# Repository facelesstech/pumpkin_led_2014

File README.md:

pumpkin_led_2014
================

Candle replacement for a Halloween pumpkin 2014 edition

Blog post explaining it all can be found here

https://facelesstech.wordpress.com/2014/10/30/pumpkin-candle-replacement-2014-edition-pumpkin_led/

Video of pumpkin led in action

http://youtu.be/Q0YgAvuTLzo?list=UUuK2SlZlnsWDYSvBv1lbuAwhttp://youtu.be/Q0YgAvuTLzo?list=UUuK2SlZlnsWDYSvBv1lbuAw

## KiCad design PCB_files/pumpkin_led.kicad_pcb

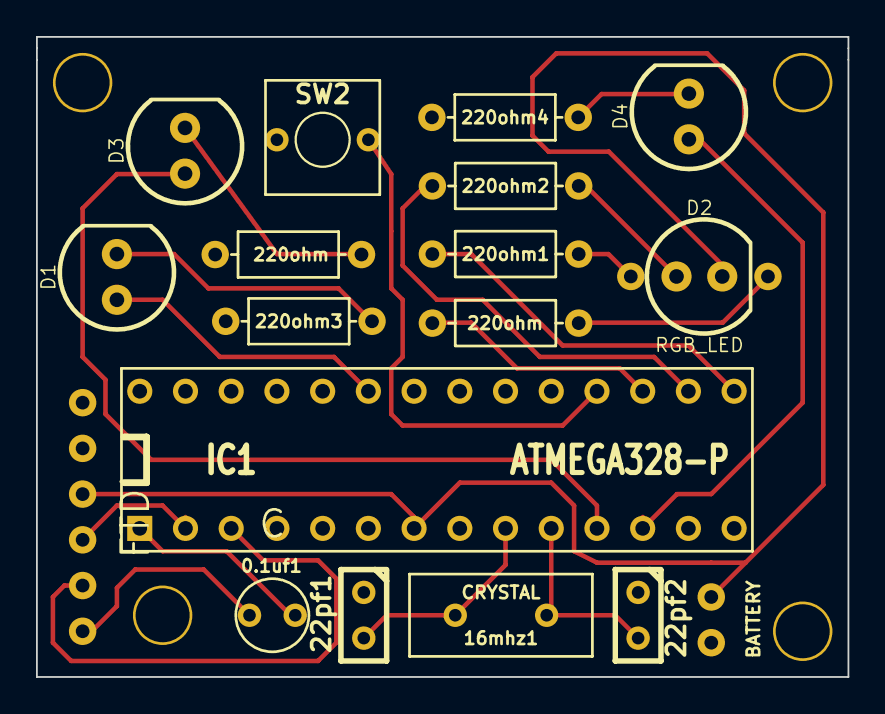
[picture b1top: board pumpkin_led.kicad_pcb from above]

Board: 2 copper layers, 45.1 x 35.6 mm, 22 parts (0 on the bottom side), 21 nets.

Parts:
0.1uf1: C; cap_2.54x4.20
16mhz1: CRYSTAL; horizontal_crystal_10mm
22pf1, 22pf2: C; Capacitor3MMDiscRM2.5
220ohm1, 220ohm2, 220ohm3, 220ohm4: R; resistor_8mm
BT1: BATTERY; Battery_AA
D1, D3, D4: LED; LED_5MM_basic
D2: RGB_LED; LED_RGB_Basic
FTDI1: FTDI; FTDI_Header
IC1: ATMEGA328-P; DIP-28_Socket
M4_Mount_Hole, M4_Mount_Hole#2, M4_Mount_Hole#3, M4_Mount_Hole#4: VAL**; M4_Mount_Hole
R1, R2: 220ohm; resistor_8mm
SW2: SW_PUSH; Push_button_single

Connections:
GND: 22pf1.1, 22pf2.1, 220ohm3.1, 220ohm4.1, BT1.2, FTDI1.1, IC1.8, R2.1, SW2.1
unnamed: 0.1uf1.1, FTDI1.6
unnamed: 0.1uf1.2, IC1.1
unnamed: 16mhz1.1, 22pf1.2, IC1.9
unnamed: 16mhz1.2, 22pf2.2, IC1.10
unnamed: 220ohm1.1, D2.1
unnamed: 220ohm1.2, IC1.15
unnamed: 220ohm2.1, D2.2
unnamed: 220ohm2.2, IC1.16
unnamed: 220ohm3.2, D1.2
unnamed: 220ohm4.2, D4.2
unnamed: D1.1, IC1.23
unnamed: D2.4, R1.1
unnamed: D3.1, IC1.11
unnamed: D3.2, R2.2
unnamed: D4.1, IC1.12
unnamed: FTDI1.4, IC1.2
unnamed: FTDI1.5, IC1.3
unnamed: IC1.17, R1.2
unnamed: IC1.18, SW2.2
VCC: BT1.1, D2.3, FTDI1.3, IC1.7

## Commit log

2014-10-06 Files to make the pcb if you wish
2014-10-06 libiary files for the pcb
2014-10-07 Breadboard layout
2014-10-27 finalish code still needs more comments
2014-10-27 Added comments
2014-11-15 removed a folder
2014-11-15 Cleaned up code and added a splash screen
2014-11-15 added blog post url
2014-11-15 Added video URL
